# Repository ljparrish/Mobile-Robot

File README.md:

# Mobile-Robot
Final Project for ME235 - Autonomous Mobile Robot

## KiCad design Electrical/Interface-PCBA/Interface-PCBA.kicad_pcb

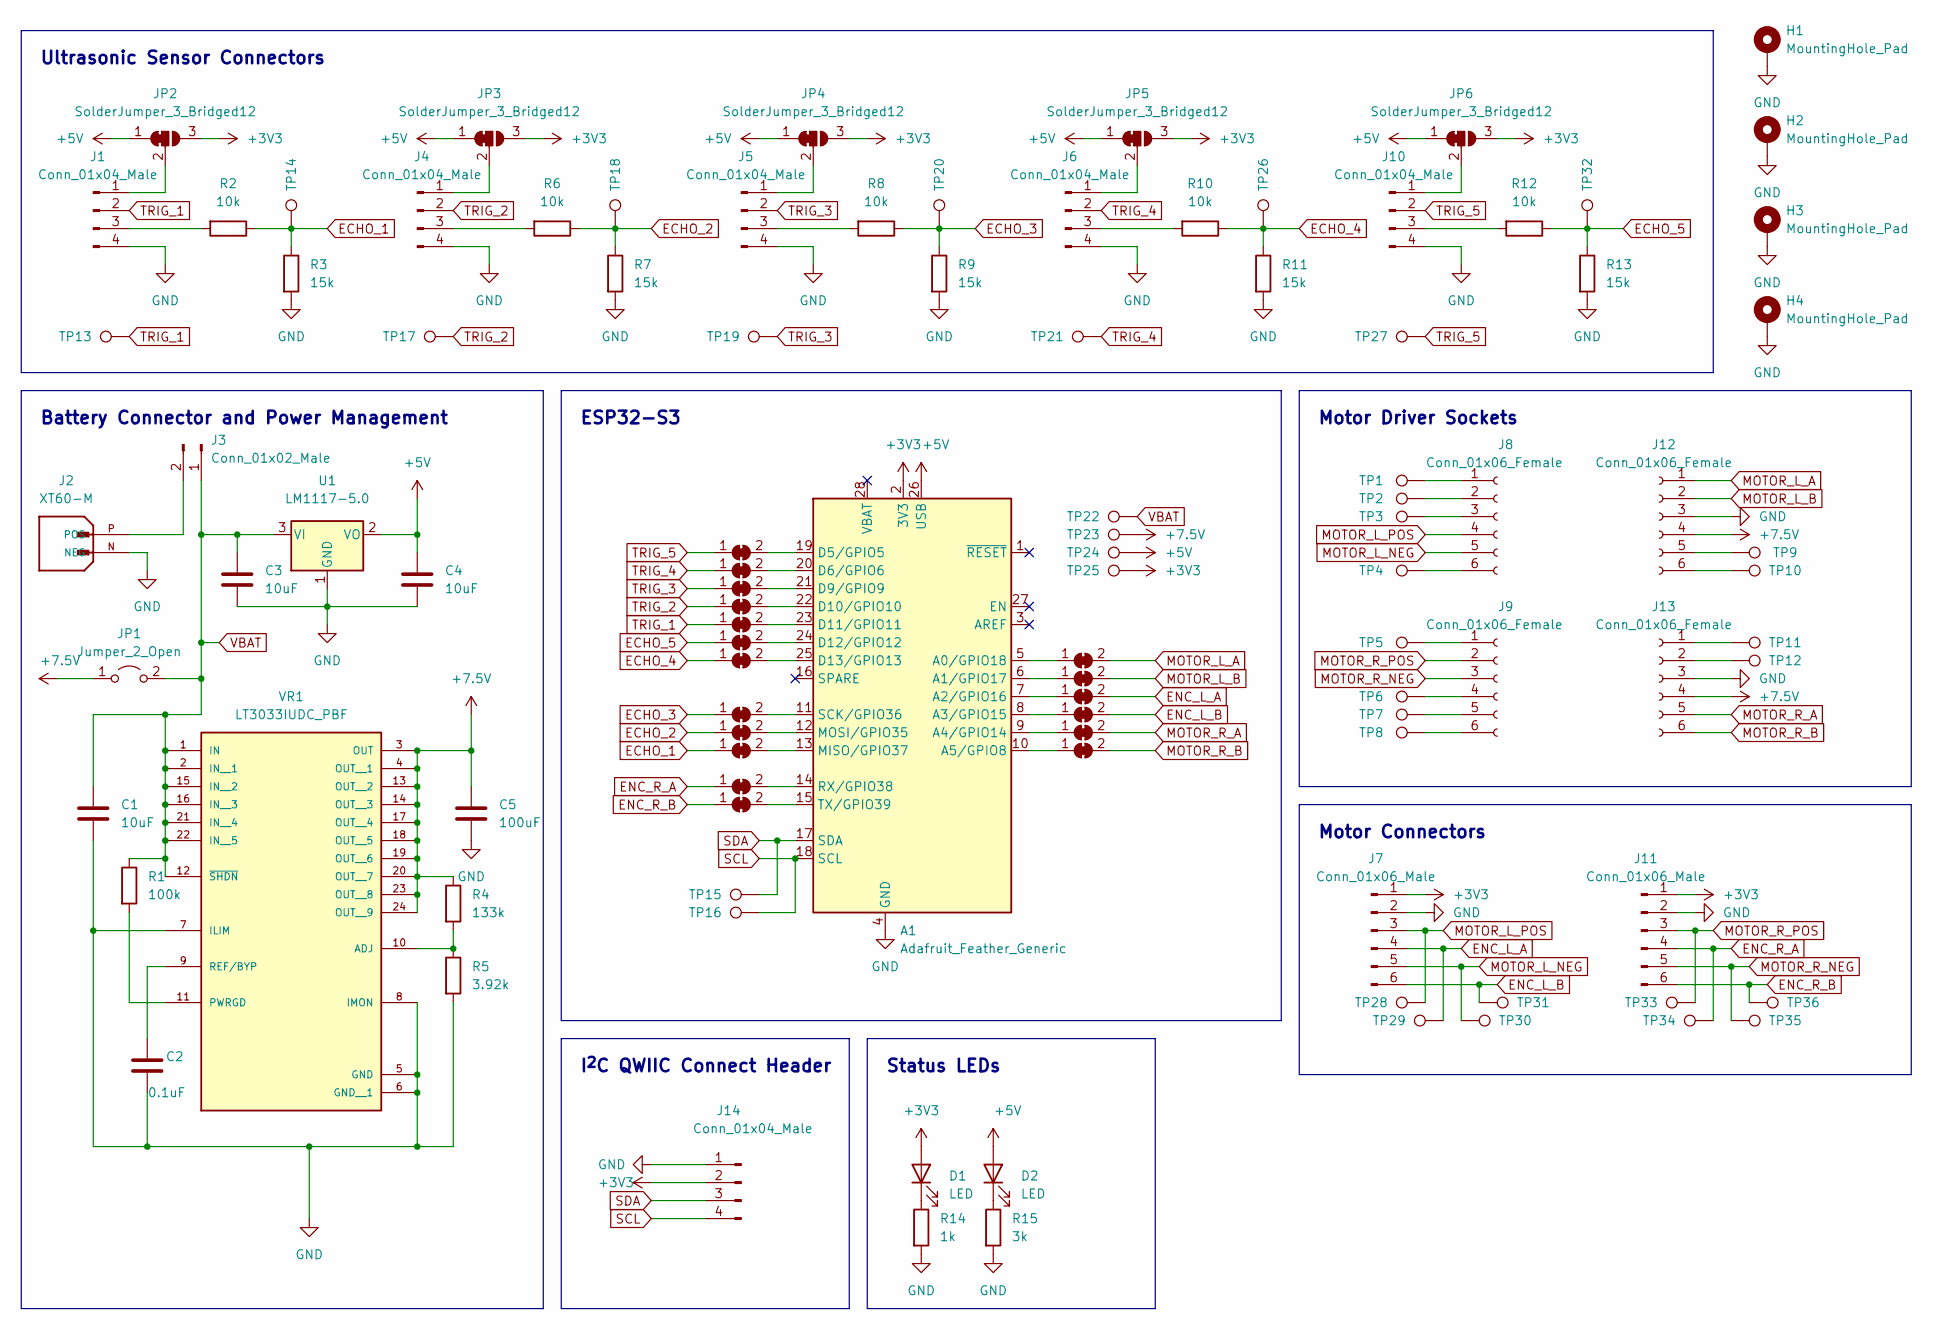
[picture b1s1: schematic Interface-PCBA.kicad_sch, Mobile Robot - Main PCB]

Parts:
A1: Adafruit_Feather_Generic; Adafruit_Feather
C1, C3, C4: 10uF; CP_EIA-3216-18_Kemet-A
C2: 0.1uF; R_0603_1608Metric
C5: 100uF; CP_EIA-3216-18_Kemet-A
D1, D2: LED; LED_0603_1608Metric_Pad1.05x0.95mm_HandSolder
H1, H2, H3, H4: MountingHole_Pad; MountingHole_3.2mm_M3_DIN965_Pad
J1, J4, J5, J6, J10: Conn_01x04_Male; JST_XH_S4B-XH-A-1_1x04_P2.50mm_Horizontal
J2: XT60-M; AMASS_XT60-M; PARTREV V1.2
J3: Conn_01x02_Male; JST_XH_B2B-XH-A_1x02_P2.50mm_Vertical
J7, J11: Conn_01x06_Male; JST_XH_B6B-XH-A_1x06_P2.50mm_Vertical
J8, J9, J12, J13: Conn_01x06_Female; PinSocket_1x06_P2.54mm_Vertical
J14: Conn_01x04_Male; JST_SH_SM04B-SRSS-TB_1x04-1MP_P1.00mm_Horizontal
JP1: Jumper_2_Open; R_0805_2012Metric
JP2, JP3, JP4, JP5, JP6: SolderJumper_3_Bridged12; SolderJumper-3_P1.3mm_Bridged12_Pad1.0x1.5mm_NumberLabels
JP7, JP8, JP9, JP10, JP11, JP12, JP13, JP14, JP15, JP16, JP17, JP18, JP19, JP20, JP21, JP22, JP23, JP24: SolderJumper_2_Bridged; SolderJumper-2_P1.3mm_Bridged_RoundedPad1.0x1.5mm
R1: 100k; R_0805_2012Metric
R2, R6, R8, R10, R12: 10k; R_0805_2012Metric
R3, R7, R9, R11, R13: 15k; R_0805_2012Metric
R4: 133k; R_0805_2012Metric
R5: 3.92k; R_0805_2012Metric
R14: 1k; R_0805_2012Metric
R15: 3k; R_0805_2012Metric
TP1, TP2, TP3, TP4, TP5, TP6, TP7, TP8, TP9, TP10, TP11, TP12: TestPoint; TestPoint_Pad_D1.5mm
TP13, TP14, TP15, TP16, TP17, TP18, TP19, TP20, TP21, TP22, TP23, TP24, TP25, TP26, TP27, TP28, TP29, TP30, TP31, TP32, TP33, TP34, TP35, TP36: TestPoint; TestPoint_2Pads_Pitch2.54mm_Drill0.8mm
U1: LM1117-5.0; SOT-223
VR1: LT3033IUDC_PBF; VREG_LT3033IUDC_PBF; PARTREV A

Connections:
+3V3: A1.2 (3V3), D1.2 (A), J7.1, J11.1, J14.2, JP2.3 (B), JP3.3 (B), JP4.3 (B), JP5.3 (B), JP6.3 (B), TP25.1
+5V: A1.26 (USB), C4.1, D2.2 (A), JP2.1 (A), JP3.1 (A), JP4.1 (A), JP5.1 (A), JP6.1 (A), TP24.1, U1.2 (VO)
+7.5V: C5.1, J12.4, J13.4, JP1.1 (A), R4.1, TP23.1, VR1.3 (OUT), VR1.4 (OUT__1), VR1.13 (OUT__2), VR1.14 (OUT__3), VR1.17 (OUT__4), VR1.18 (OUT__5), VR1.19 (OUT__6), VR1.20 (OUT__7), VR1.23 (OUT__8), VR1.24 (OUT__9)
ECHO_1: JP16.1 (A), R2.1, R3.1, TP14.1
ECHO_2: JP15.1 (A), R6.1, R7.1, TP18.1
ECHO_3: JP14.1 (A), R8.1, R9.1, TP20.1
ECHO_4: JP13.1 (A), R10.1, R11.1, TP26.1
ECHO_5: JP12.1 (A), R12.1, R13.1, TP32.1
ENC_L_A: J7.4, JP21.2 (B), TP29.1
ENC_L_B: J7.6, JP22.2 (B), TP31.1
ENC_R_A: J11.4, JP17.1 (A), TP34.1
ENC_R_B: J11.6, JP18.1 (A), TP36.1
GND: A1.4 (GND), C1.2, C2.2, C3.2, C4.2, C5.2, H1.1, H2.1, H3.1, H4.1, J1.4, J2.N (NEG), J4.4, J5.4, J6.4, J7.2, J10.4, J11.2, J12.3, J13.3, J14.1, R3.2, R5.2, R7.2, R9.2, R11.2, R13.2, R14.2, R15.2, U1.1 (GND), VR1.5 (GND), VR1.6 (GND__1), VR1.7 (ILIM), VR1.8 (IMON)
MOTOR_L_A: J12.1, JP19.2 (B)
MOTOR_L_B: J12.2, JP20.2 (B)
MOTOR_L_NEG: J7.5, J8.5, TP30.1
MOTOR_L_POS: J7.3, J8.4, TP28.1
MOTOR_R_A: J13.5, JP23.2 (B)
MOTOR_R_B: J13.6, JP24.2 (B)
MOTOR_R_NEG: J9.3, J11.5, TP35.1
MOTOR_R_POS: J9.2, J11.3, TP33.1
unnamed: A1.5 (A0/GPIO18), JP19.1 (A)
unnamed: A1.6 (A1/GPIO17), JP20.1 (A)
unnamed: A1.7 (A2/GPIO16), JP21.1 (A)
unnamed: A1.8 (A3/GPIO15), JP22.1 (A)
unnamed: A1.9 (A4/GPIO14), JP23.1 (A)
unnamed: A1.10 (A5/GPIO8), JP24.1 (A)
unnamed: A1.11 (SCK/GPIO36), JP14.2 (B)
unnamed: A1.12 (MOSI/GPIO35), JP15.2 (B)
unnamed: A1.13 (MISO/GPIO37), JP16.2 (B)
unnamed: A1.14 (RX/GPIO38), JP17.2 (B)
unnamed: A1.15 (TX/GPIO39), JP18.2 (B)
unnamed: A1.19 (D5/GPIO5), JP7.2 (B)
unnamed: A1.20 (D6/GPIO6), JP8.2 (B)
unnamed: A1.21 (D9/GPIO9), JP9.2 (B)
unnamed: A1.22 (D10/GPIO10), JP10.2 (B)
unnamed: A1.23 (D11/GPIO11), JP11.2 (B)
unnamed: A1.24 (D12/GPIO12), JP12.2 (B)
unnamed: A1.25 (D13/GPIO13), JP13.2 (B)
unnamed: C2.1, VR1.9 (REF/BYP)
unnamed: D1.1 (K), R14.1
unnamed: D2.1 (K), R15.1
unnamed: J1.1, JP2.2 (C)
unnamed: J1.3, R2.2
unnamed: J2.P (POS), J3.2
unnamed: J4.1, JP3.2 (C)
unnamed: J4.3, R6.2
unnamed: J5.1, JP4.2 (C)
unnamed: J5.3, R8.2
unnamed: J6.1, JP5.2 (C)
unnamed: J6.3, R10.2
unnamed: J8.1, TP1.1
unnamed: J8.2, TP2.1
unnamed: J8.3, TP3.1
unnamed: J8.6, TP4.1
unnamed: J9.1, TP5.1
unnamed: J9.4, TP6.1
unnamed: J9.5, TP7.1
unnamed: J9.6, TP8.1
unnamed: J10.1, JP6.2 (C)
unnamed: J10.3, R12.2
unnamed: J12.5, TP9.1
unnamed: J12.6, TP10.1
unnamed: J13.1, TP11.1
unnamed: J13.2, TP12.1
unnamed: R1.2, VR1.11 (PWRGD)
unnamed: R4.2, R5.1, VR1.10 (ADJ)
SCL: A1.18 (SCL), J14.4, TP16.1
SDA: A1.17 (SDA), J14.3, TP15.1
TRIG_1: J1.2, JP11.1 (A), TP13.1
TRIG_2: J4.2, JP10.1 (A), TP17.1
TRIG_3: J5.2, JP9.1 (A), TP19.1
TRIG_4: J6.2, JP8.1 (A), TP21.1
TRIG_5: J10.2, JP7.1 (A), TP27.1
VBAT: C1.1, C3.1, J3.1, JP1.2 (B), R1.1, TP22.1, U1.3 (VI), VR1.1 (IN), VR1.2 (IN__1), VR1.12 (~SHDN), VR1.15 (IN__2), VR1.16 (IN__3), VR1.21 (IN__4), VR1.22 (IN__5)

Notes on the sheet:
I^{2}C QWIIC Connect Header
Status LEDs
Motor Connectors
Battery Connector and Power Management
ESP32-S3
Ultrasonic Sensor Connectors
Motor Driver Sockets

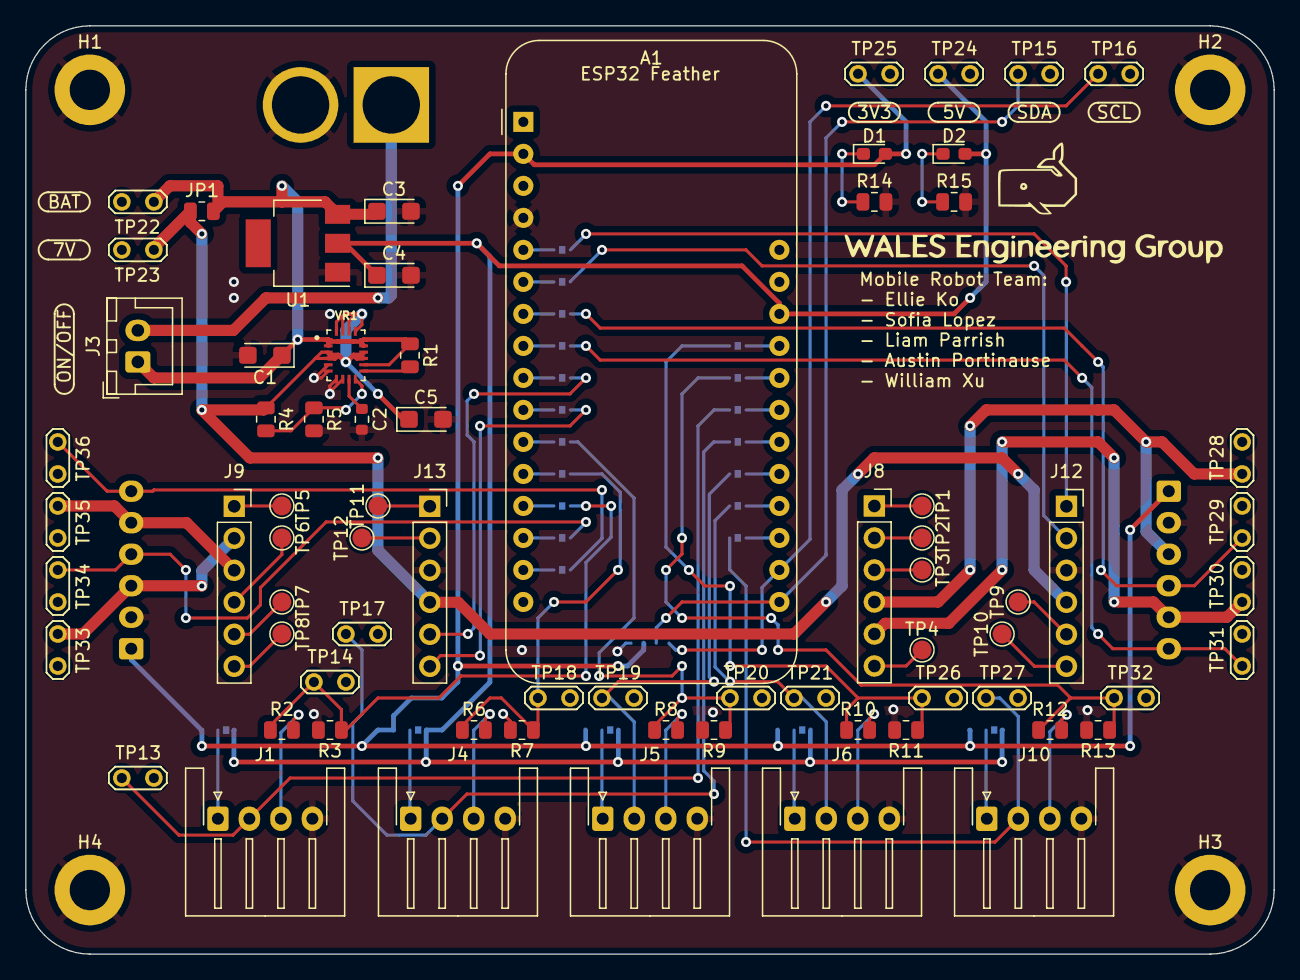
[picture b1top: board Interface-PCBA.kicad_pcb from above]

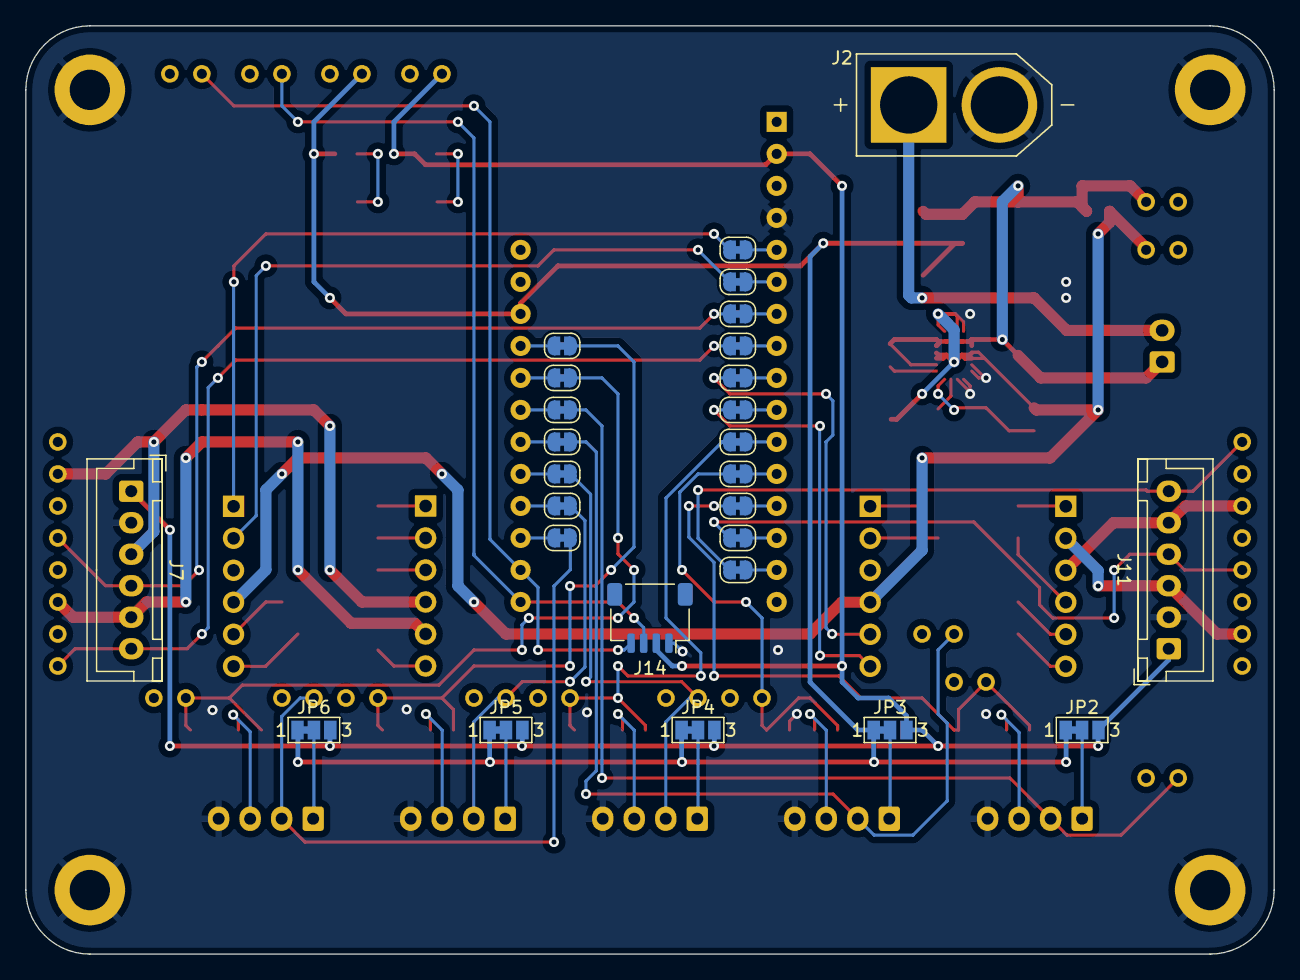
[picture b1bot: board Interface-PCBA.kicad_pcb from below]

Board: 2 copper layers, 99.1 x 73.7 mm, 103 parts (27 on the bottom side), 75 nets.

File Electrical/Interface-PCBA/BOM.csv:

"Id";"Designator";"Package";"Quantity";"Designation";"Supplier and ref";
1;"J12,J9,J8,J13";"PinSocket_1x06_P2.54mm_Vertical";4;"Conn_01x06_Female";;;
2;"R1";"R_0805_2012Metric";1;"100k";;;
3;"JP1";"R_0805_2012Metric";1;"Jumper_2_Open";;;
4;"C5";"CP_EIA-3216-18_Kemet-A";1;"100uF";;;
5;"TP1,TP3,TP6,TP2,TP9,TP8,TP10,TP5,TP4,TP11,TP7,TP12";"TestPoint_Pad_D1.5mm";12;"TestPoint";;;
6;"R14";"R_0805_2012Metric";1;"1k";;;
7;"TP14,TP24,TP26,TP13,TP25,TP27,TP16,TP19,TP29,TP23,TP15,TP17,TP32,TP20,TP36,TP30,TP31,TP18,TP34,TP22,TP33,TP21,TP28,TP35";"TestPoint_2Pads_Pitch2.54mm_Drill0.8mm";24;"TestPoint";;;
8;"J4,J1,J5,J6,J10";"JST_XH_S4B-XH-A-1_1x04_P2.50mm_Horizontal";5;"Conn_01x04_Male";;;
9;"H4,H1,H3,H2";"MountingHole_3.2mm_M3_DIN965_Pad";4;"MountingHole_Pad";;;
10;"R8,R6,R12,R10,R2";"R_0805_2012Metric";5;"10k";;;
11;"D1,D2";"LED_0603_1608Metric_Pad1.05x0.95mm_HandSolder";2;"LED";;;
12;"R3,R13,R11,R7,R9";"R_0805_2012Metric";5;"15k";;;
13;"R15";"R_0805_2012Metric";1;"3k";;;
14;"C4,C3,C1";"CP_EIA-3216-18_Kemet-A";3;"10uF";;;
15;"R4";"R_0805_2012Metric";1;"133k";;;
16;"C2";"R_0603_1608Metric";1;"0.1uF";;;
17;"A1";"Adafruit_Feather";1;"Adafruit_Feather_Generic";;;
18;"VR1";"VREG_LT3033IUDC_PBF";1;"LT3033IUDC_PBF";;;
19;"R5";"R_0805_2012Metric";1;"3.92k";;;
20;"U1";"SOT-223";1;"LM1117-5.0";;;
21;"J3";"JST_XH_B2B-XH-A_1x02_P2.50mm_Vertical";1;"Conn_01x02_Male";;;
22;"JP11,JP12,JP13,JP19,JP24,JP8,JP14,JP18,JP10,JP16,JP17,JP7,JP21,JP9,JP22,JP15,JP23,JP20";"SolderJumper-2_P1.3mm_Bridged_RoundedPad1.0x1.5mm";18;"SolderJumper_2_Bridged";;;
23;"J7,J11";"JST_XH_B6B-XH-A_1x06_P2.50mm_Vertical";2;"Conn_01x06_Male";;;
24;"JP6,JP4,JP2,JP3,JP5";"SolderJumper-3_P1.3mm_Bridged12_Pad1.0x1.5mm_NumberLabels";5;"SolderJumper_3_Bridged12";;;
25;"J2";"AMASS_XT60-M";1;"XT60-M";;;
26;"J14";"JST_SH_SM04B-SRSS-TB_1x04-1MP_P1.00mm_Horizontal";1;"Conn_01x04_Male";;;

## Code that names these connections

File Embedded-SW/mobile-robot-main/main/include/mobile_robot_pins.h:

/*  Mobile Robot Pinout

    This header file contains signal names defined by the mobile robot adapter board schematic.
    Note: Names are exactly as written on the schematic.
*/

#include <stdio.h>
#include "sdkconfig.h"
#include "driver/gpio.h"

// Motor I/O
#define MOTOR_L_A GPIO_NUM_18
#define MOTOR_L_B GPIO_NUM_17
#define MOTOR_R_A GPIO_NUM_14
#define MOTOR_R_B GPIO_NUM_8

// Encoder I/O
#define ENC_L_A GPIO_NUM_16
#define ENC_L_B GPIO_NUM_15
#define ENC_R_A GPIO_NUM_38
#define ENC_R_B GPIO_NUM_39

// Ultrasonic Sensors
#define TRIG_1 GPIO_NUM_11
#define TRIG_2 GPIO_NUM_10
#define TRIG_3 GPIO_NUM_9
#define TRIG_4 GPIO_NUM_6
#define TRIG_5 GPIO_NUM_5

#define ECHO_1 GPIO_NUM_37
#define ECHO_2 GPIO_NUM_35
#define ECHO_3 GPIO_NUM_36
#define ECHO_4 GPIO_NUM_13
#define ECHO_5 GPIO_NUM_12

// Neopixel LED
#define NEOPIXEL_POWER GPIO_NUM_21
#define NEOPIXEL_ADDRESS GPIO_NUM_33

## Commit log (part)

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2024-02-23 Interface PCB Rev 1
    Created first iteration of PCB for connecting ESP32 to periphrials
2024-02-29 PCB Design
    Finished PCB design and sent out for fabrication
2024-03-01 Created Path Planning VI
    - First pass at creating a VI for A* path planning
2024-03-05 Created PathPlanningSim
2024-03-06 Updated PathPlanningSim
    Creating statements to check if where the robot is. If on the edge or corner, the robot will check less values to see if there are obstacles around it.
2024-03-07 Updated PathPlanning
2024-03-09 Updated PathPlanning
    Need to figure out how to prevent updated grid values from resetting each iteration in while loop
2024-03-10 Finished Prelim Path Planning
2024-03-10 Created MPC Controller for Unicycle Robot
    - Created non-linear mpc model of unicycle following a parameterized trajectory
2024-03-10 Updates to PCBA BOM files
2024-03-10 Create .gitignore for MATLAB folder
2024-03-12 rotary encoder example
    edited example from ESP IDF
2024-03-13 Create PathPlanning Matlab file
2024-03-14 PathPlanning updates
2024-03-14 Updated Unicycle model with wheel velocity inputs
2024-03-14 Update MobileRobotMPC.m
    - Updated plot labels
2024-03-15 Updated Path Planning
2024-03-15 Updated Waypoint Generation
2024-03-15 Created AStar Path Planning
2024-03-16 Added support for path planned trajectories
2024-03-18 Create A*Regular
2024-03-18 Started MATLAB GUI
    - Created MATLAB Application
2024-03-20 Update GUI
2024-03-20 Got 2 encoders working!
    rotary_encoder_example_main: the pure example from ESP documentation for reading encoder pulses, one wheel.
    encoder_example_trim_down: trim down ESP example to get rid of unnecessary items. Added accum count, counts total pulses, no more watch points.
    two_wheels_encoder_reading: outputs accum count for encoder pulses for two wheels. Resets count to 0 at each time interval. USE THIS ONE for main file.
    multitasking_try1: skeleton code for multitasking from this youtube video :https://www.youtube.com/watch?v=bEhZp4Adghc
2024-03-21 Update MobileRobotMPC.m
    - Added moveMPC functions compatible with codegen
2024-03-21 Setup Embedded Systems Project Folder
    - Added skeleton for main mobile robot script with RTOS multitasking
    - Added basic LED blink task
    - Added header file for PCB pinout
2024-03-21 Added Motor Control
    - Added motor control and PID libraries
    - Made basic motor control ramp function
2024-03-22 Added comments to C code
2024-03-24 Updated VS Code setttings JSON file
    - Removed computer specific parameters from JSON file, project should now be configured for building on other computers
2024-03-26 Implemented Motor PID
    - Added Sofia's code for encoder measurement
    - Added encoder measurement Queue for sending data
    - Added motor closed loop control
2024-04-01 GUI Update
2024-04-02 Integrate MPC/Path Planning into GUI
2024-04-02 Started setting up ESPNOW wireless code
2024-04-03 Updated GUI
2024-04-03 added serial port com folder
2024-04-03 ESP NOW Updates
    - Finished first pass of ESPNOW code for mobile robot
    - Currently sends test data that increments in software
2024-04-03 Fixed MPC Stuff, need to update it on GUI
2024-04-03 Add simple state estimation
    - Not complete
    - Comments share the issue to be fixed
2024-04-03 GUI MPC Finished
2024-04-03 Added Unicycle functions into same folder
2024-04-05 Updated GUI and serial comms
2024-04-05 Update MobileRobotControlGUI.mlapp
    Added plotting of xy trajectory
2024-04-07 Add state estimation to main source code
2024-04-07 Add the code used to test algorithms
    - Tested state estimation in Python and C
    - Tested three ultrasonic sensor measurement
2024-04-07 Move state estimation macros below encoder macros
2024-04-09 Created USB dongle ESP-IDF Project
    Setup project folder for USB wireless dongle using ESP32-C3
2024-04-09 Update Serial Comm
2024-04-09 Fix state estimation initialization issue and add scaling factor
2024-04-09 Started UART.c File
2024-04-09 Add ultrasonic sensor measurement task
2024-04-09 Added base code for ESP NOW dongle
2024-04-09 Updated Serial Com GUI
2024-04-09 Small code edit to reflect mobile robot address
2024-04-09 Update main.c
    - Added code to output MAC Address of ESP32
2024-04-10 Started implementing Queues for sending data over espnow
2024-04-10 Added debug statements
2024-04-10 Update Mobile GUI
2024-04-10 Small edits to dongle code
2024-04-10 ESP NOW Robot side code
2024-04-11 Playing around with path planning
2024-04-13 UART Debugging
2024-04-13 Update MobileRobotControlGUI.mlapp
    - Fixed trajectory planning time scaling problem
    - Added points at end of robot trajectory to bring robot to a stop when it reaches its target
2024-04-14 Simplified basic UART Test
2024-04-15 Keyboard Commands Updated onto GUI
2024-04-16 Updated Plotting Code
2024-04-16 Dongle UART and Wireless
    - Added UART configuration for dongle
    - Updated ESP NOW structure to be smaller
    - Wrote task functions and setup queues for 2 way data transmission
2024-04-16 Update esp_now_structures.h
    Updated to match dongle side
2024-04-16 Wireless Control
    - Added robot side motor command queue
    - Updated ESP NOW robot code
2024-04-16 Plotting Robot Function
2024-04-16 Update esp_now.c
    Updated MAC address for dongle
2024-04-16 Create populate occupancy grid
    :)
2024-04-17 Modified delays to sending ESP NOW data
2024-04-17 Changes to ESPNOW delays
    - Tweaked motor PID gains
2024-04-17 testing occupancy grid
    testing
2024-04-18 Remove TODO (no compile error)
2024-04-18 Change ultrasonic sensors order
2024-04-18 Updated State Estimation on GUI
2024-04-18 Added ultrasonic values to ESP NOW transmission
2024-04-18 Push GUI Code
2024-04-18 GUI Updates and Debug
2024-04-19 Add populating occupancy grid with dummy ultrasonic sensor measurements
2024-04-19 Update motor_control.c
    - Added open loop test routine
2024-04-21 Added timer callback functions to GUI
2024-04-21 System ID for DC motor
    - Gathered data for system ID of the DC motor
    - Fit motor model to experimental data
2024-04-21 Edits to main for motor testing
2024-04-22 Added DC Motor Feedforward
    - Added new feedforward commands
    - Implemented in main
2024-04-22 Updated PID Gains
2024-04-22 Updated GUI
    Have MPC Inputs sent over a time object. Have control input plot working for manual control but its not working for automated control. There seems to be something wrong with the state estimation as w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
2024-04-22 create UpdateOccupancyGrid function
2024-04-23 Changes to ESP now structure
2024-04-23 Update ESP_NOW to send prev cmd if nothing received
2024-04-23 Update PID Control to stop robot if it loses connection
2024-04-23 created grid library
2024-04-23 Created and updated Version 2 GUI
2024-04-24 Fixed mobile robot transmitting odometry
2024-04-24 Updated GUI
    - Updated plotting
2024-04-24 Update motor_control.c
    - Updated robot initial position
2024-04-24 Added functionality to reset and load occupant grid
    need to test greatly
2024-04-24 Updated Load Occupancy grid on GUI
2024-04-24 occupancy grid shows up on robot env plot
2024-04-25 Updated ESP Data Transfer Rate
2024-04-25 Trying to fix plotting for the Autonomous control
2024-04-25 Create PlottingTest.mlapp
    - Added simple plotting GUI for testing
2024-04-26 Fixed GUI Issues
    Added Legend Pictures, Added occupancy grid to display when path planning, added debug tab, added consistent scaling for trajectory plot
2024-04-26 Update Version2_MobileRobotControlGUI.mlapp
    Moved GUI Legend to top right of env. plot
2024-04-26 Updated GUI
    Updated the manual control tab to include a control switch rather than a button to start and disable manual control
2024-04-26 Update motor_control.c
    - Changed scaling factors
2024-04-27 Update ultrasonic sensor measurement to detect non-occupancy and fix typos
2024-04-27 Updated Motor Control
2024-04-27 Update main.c
    Changed PID from incremental to positional
2024-04-30 Started V4 for updated plots
2024-04-30 Updated GUI occupancy
2024-04-30 Started new branch with timer interrupt
2024-05-01 Edit ultrasonic sensor measurements (max range, timeout)
2024-05-01 Fix ultrasonic sensor's the max range to 255
2024-05-01 Set Tasks to run on specific cores
2024-05-01 Improved Plotting Speed
2024-05-01 Pushed Whale Sounds
2024-05-01 Changed feedforward coeff
2024-05-01 Updated the GUI
2024-05-01 Update Version5_MobileRobotControlGUI.mlapp
    Added progress bar for path planning
2024-05-01 Update main.c
    Final changes to code
2024-05-02 Update main.c
    Updated code multitasking priorities
2024-05-09 Started Explicit MPC controller
    - Added .m for computing policy
    - Added .m for simulating policy
2024-05-10 Updated Name
2025-02-24 Started Python GUI for Mobile Robot
    - Created basic gui functionality
    -- Serial port connect and data log
    -- Serial port send command for wheel speeds
    -- Basic plotting for X, Y, and T
2025-02-28 Pygui update
    -Updated embedded code on robot to avoid motor crashing
    - Added robot environment plot to GUI
